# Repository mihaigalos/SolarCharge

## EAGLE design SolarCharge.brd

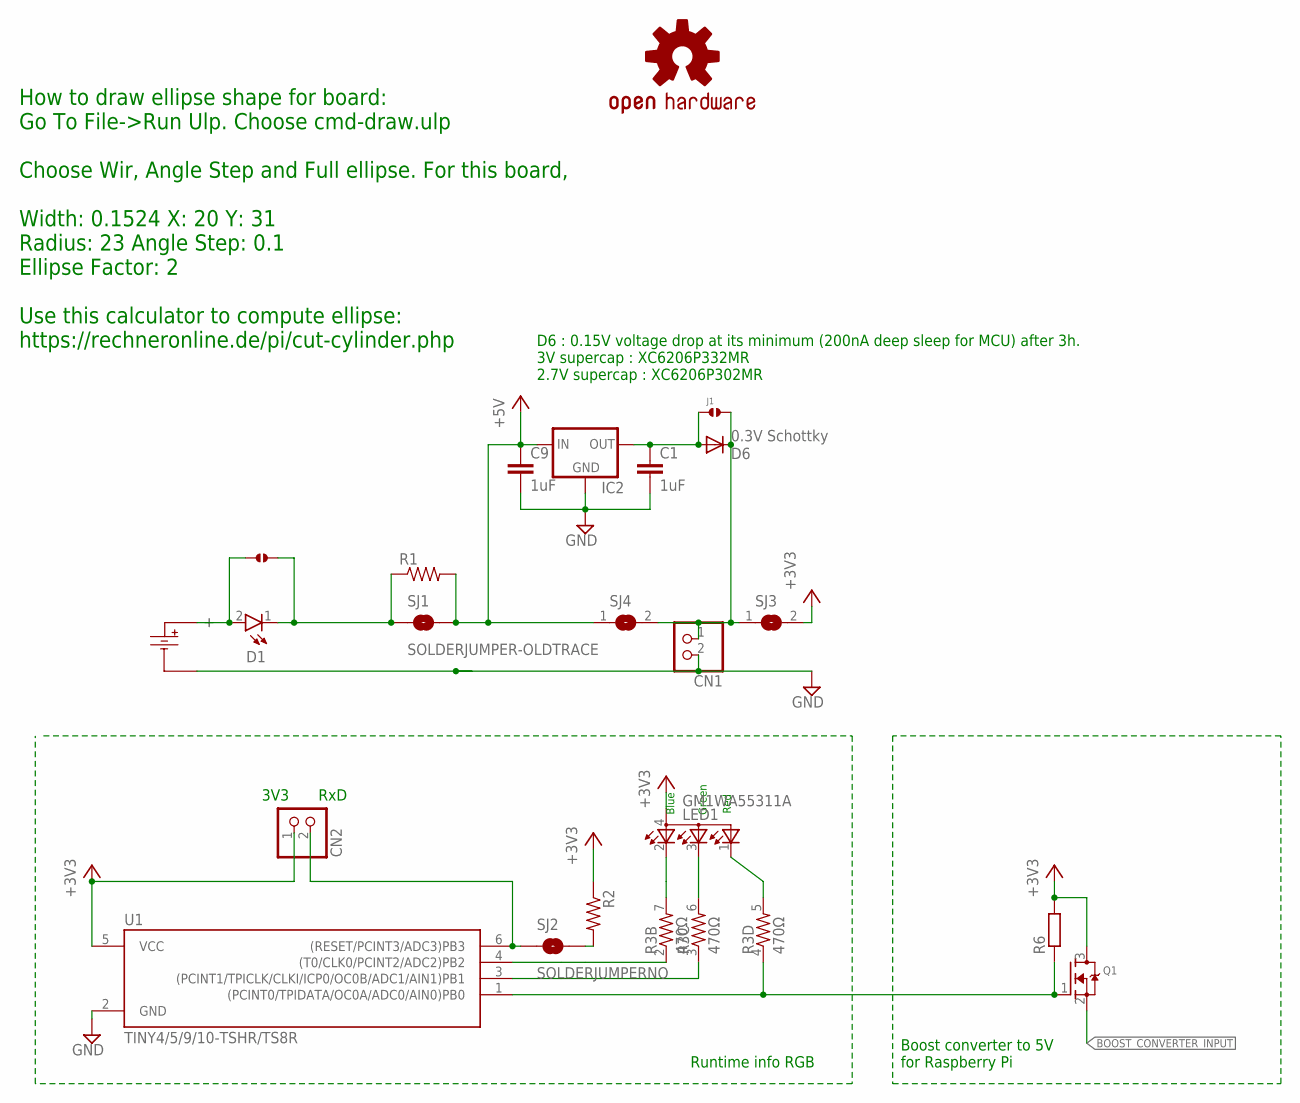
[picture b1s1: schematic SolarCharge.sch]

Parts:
C1, C9: 1uF; C0603
CN1, CN2: JST_2PIN-SMT-RA; JST-PH-2-SMT-RA
D1: WL-SWTP3014; WL-SWTP_3014
D6: 0.3V Schottky; SOD523
IC2: MCP1700TT; SOT-23
J1: SOLDERJUMPER.2.MED; 2.MED
J3: SOLDERJUMPER.2.XL; 2.XL
LED1: GM1WA55311A
LOGO1: OSHW-LOGOM; OSHW-LOGO-M
Q1: MOSFET-NREFLOW; SOT23
R1, R2: RESISTOR0603-RES; 0603-RES
R3: 470Ω; 0603-ARV
R6: R-EU_R0603; R0603
SJ1: SOLDERJUMPER-OLDTRACE; SJ_2S-TRACE
SJ2: SOLDERJUMPERNO; SJ_2S-NO
SJ3, SJ4: SJ
U1: TINY4/5/9/10-TSHR/TS8R; SOT-23-6
U$1: SOLAR_CELL_53_30

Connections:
+3V3: CN2.1 (2), LED1.4 (A), Q1.3 (D), R2.1, R6.2, SJ3.2, U1.5 (VCC)
+5V: C9.1, IC2.3 (IN), R1.2, SJ1.2, SJ4.1
BLUE: R3.3 (1), U1.3 ((PCINT1/TPICLK/CLKI/ICP0/OC0B/ADC1/AIN1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)
BOOST_CONVERTER_INPUT: Q1.2 (S)
GND: C1.2, C9.2, CN1.2 (1), IC2.1 (GND), U1.2 (GND), U$1.P$2
GREEN: R3.2 (1), U1.4 ((T0/CLK0/PCINT2/ADC2)PB2)
unnamed: D1.2, J3.1, U$1.P$1
unnamed: D1.1, J3.2, R1.1, SJ1.1
unnamed: CN1.1 (2), D6.C, J1.2, SJ3.1, SJ4.2
unnamed: LED1.3 (CBLUE), R3.6 (2)
unnamed: LED1.2 (CRED), R3.7 (2)
unnamed: R2.2, SJ2.2
unnamed: C1.1, D6.A, IC2.2 (OUT), J1.1
RED: Q1.1 (G), R3.4 (1), R6.1, U1.1 ((PCINT0/TPIDATA/OC0A/ADC0/AIN0)PB0)
RED_RESISTOR: LED1.1 (CGREEN), R3.5 (2)
RXD: CN2.2 (1), SJ2.1, U1.6 ((RESET/PCINT3/ADC3)PB3)

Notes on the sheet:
Green
Red
Blue
RxD
3V3
Runtime info RGB
Boost converter to 5V for Raspberry Pi
D6 : 0.15V voltage drop at its minimum (200nA deep sleep for MCU) after 3h. 3V supercap : XC6206P332MR 2.7V supercap : XC6206P302MR
How to draw ellipse shape for board: Go To File->Run Ulp. Choose cmd-draw.ulp Choose Wir, Angle Step and Full ellipse. For this board, Width: 0.1524 X: 20 Y: 31 Radius: 23 Angle Step: 0.1 Ellipse Factor: 2 Use this calculator to compute ellipse: https://rechneronline.de/pi/cut-cylinder.php

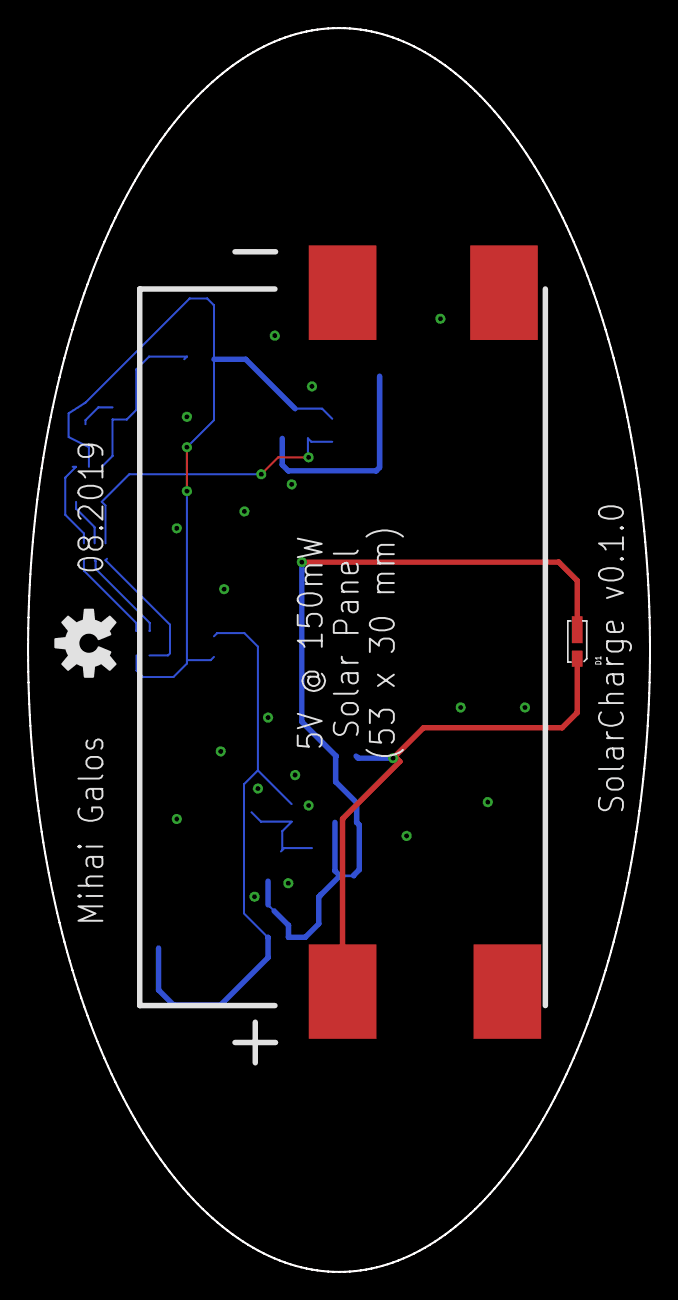
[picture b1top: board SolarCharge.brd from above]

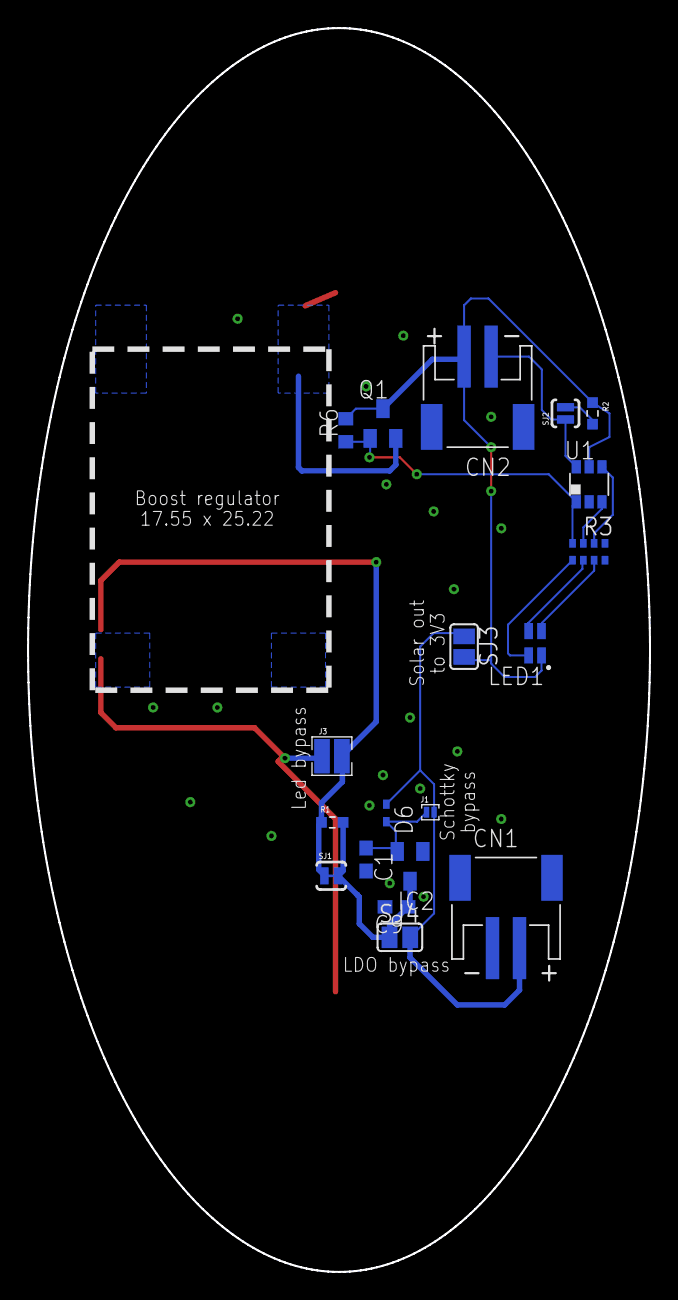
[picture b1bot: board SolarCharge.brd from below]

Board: 2 copper layers, 46.0 x 92.0 mm, 22 parts (19 on the bottom side), 15 nets.

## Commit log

2018-11-04 Improve GND
2018-11-04 Add logos, recenter
2018-11-04 Add solar panel info
2018-11-04 Realign to center
2018-11-04 Change diameter from 63.5 to 63mm
2018-11-04 Correct stray signal
2018-11-11 Add RGB runtime info
2018-11-11 Disentangle schematic resistors
2018-11-18 Add second JST connector for solar out
2018-11-18 Add Boost coverter to hookup Pi Zero W
2018-11-18 Add p-channel mosfet for latching boost converter
2019-07-06 Add overvoltage protection
2019-07-06 Fix errors
2019-07-06 Edit date
2019-07-06 Solar out to 3V3 solderjumper
2019-07-06 Use XC2606 LDO instead of Tiny10
2019-07-06 Add .gitignore
2019-07-06 Add info on how to draw ellipse in brd
2019-07-07 Add ref to online ellipse from cylinder section calculator
2019-07-07 Edit ellipse generation description
2019-07-07 Use ellipse for circle in dim layer, slanted facing sun
2019-07-07 Correct position of graphics, add pads for boost converter
2019-07-07 Readd gnd planes for ellipse
2019-07-07 Minor repositioning
2019-08-05 Remove superfluous -/+ on bPlace
2019-08-05 Increase no soldermask circle around OSHW logo
2021-01-03 Move pins further in, second row of pins for better fixture

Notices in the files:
parts and their libraries:
Wurth_Elektronik_Optoelectronics_rev15c: Copyright: Würth Elektronik
SparkFun-Passives: Licensing: CC v3.0 Share-Alike You are welcome to use this library for commercial purposes.
